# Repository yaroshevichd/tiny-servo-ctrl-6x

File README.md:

It's a try to make PWM controller on X channel using AVR MCU. MCU communication is I2C.

At local market ATtiny44A is cheapeast one, plus it have enough pins to drive 6 servos, communicate using TWI, and 3 pins to custimze address. So it's possible to drive up to (2^3 - 1) * 6 = 42 servo, which is more than enough for my requirements.

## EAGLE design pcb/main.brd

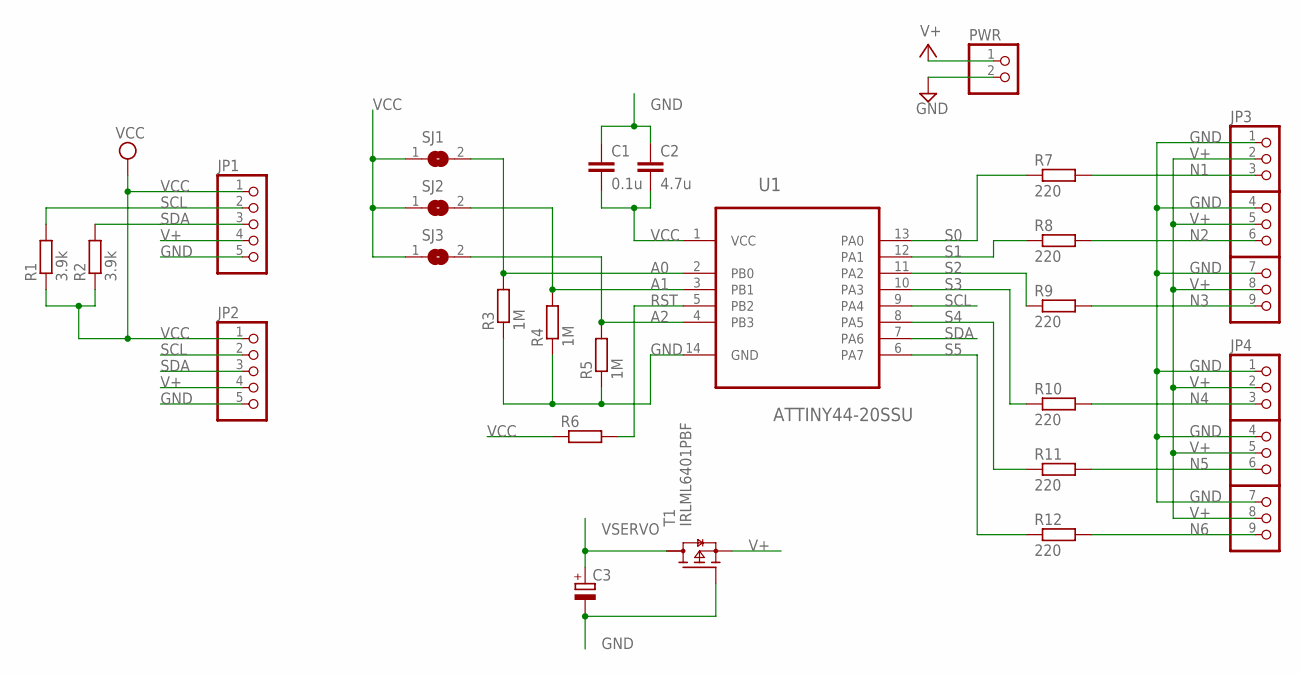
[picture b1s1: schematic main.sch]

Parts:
C1: 0.1u; C0805
C2: 4.7u; C0805
C3: CPOL-EUE2.5-6; E2,5-6
JP1, JP2: PINHD-1X5; 1X05
JP3, JP4: PINHD-3X3; 3X03
PWR: PINHD-1X2; 1X02
R1, R2: 3.9k; R0805
R3, R4, R5: 1M; R0805
R6: R-EU_R0805; R0805
R7, R8, R9, R10, R11, R12: 220; R0805
SJ1, SJ2, SJ3: SJ
T1: IRLML6401PBF; SOT23
U1: ATTINY44-20SSU; SOIC127P600X175-14N

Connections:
A0: R3.2, SJ1.2, U1.2 (PB0)
A1: R4.2, SJ2.2, U1.3 (PB1)
A2: R5.2, SJ3.2, U1.4 (PB3)
GND: C1.1, C2.1, C3.-, JP1.5, JP2.5, JP3.1, JP3.4, JP3.7, JP4.1, JP4.4, JP4.7, PWR.2, R3.1, R4.1, R5.1, T1.1 (G), U1.14 (GND)
N1: JP3.3, R7.2
N2: JP3.6, R8.2
N3: JP3.9, R9.2
N4: JP4.3, R10.2
N5: JP4.6, R11.2
N6: JP4.9, R12.2
RST: R6.2, U1.5 (PB2)
S0: R7.1, U1.13 (PA0)
S1: R8.1, U1.12 (PA1)
S2: R9.1, U1.11 (PA2)
S3: R10.1, U1.10 (PA3)
S4: R11.1, U1.8 (PA5)
S5: R12.1, U1.6 (PA7)
SCL: JP1.2, JP2.2, R1.2, U1.9 (PA4)
SDA: JP1.3, JP2.3, R2.2, U1.7 (PA6)
V+: JP1.4, JP2.4, JP3.2, JP3.5, JP3.8, JP4.2, JP4.5, JP4.8, PWR.1, T1.2 (S)
VCC: C1.2, C2.2, JP1.1, JP2.1, R1.1, R2.1, R6.1, SJ1.1, SJ2.1, SJ3.1, U1.1 (VCC)
VSERVO: C3.+, T1.3 (D)

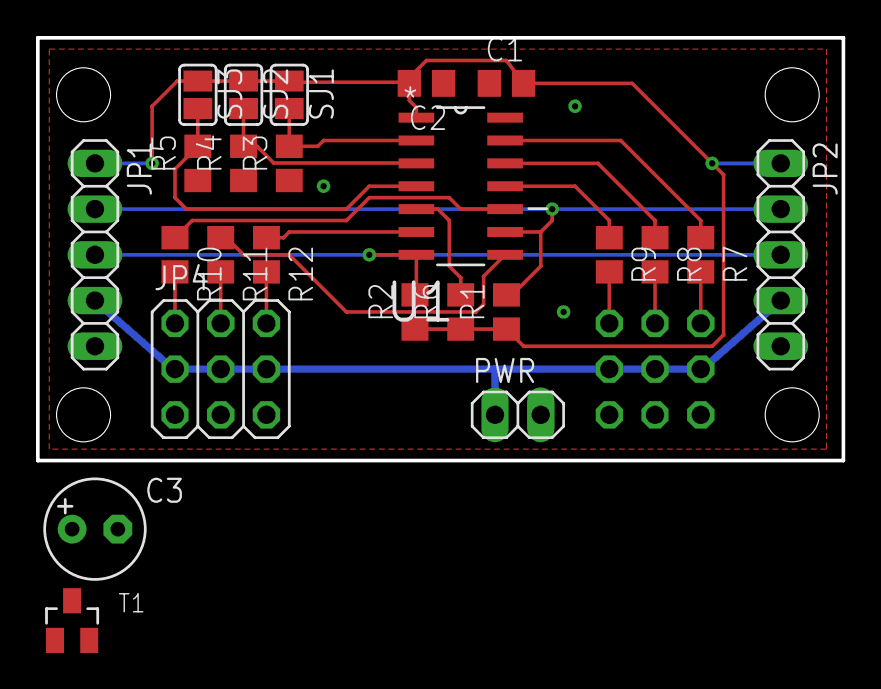
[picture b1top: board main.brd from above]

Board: 2 copper layers, 44.8 x 23.5 mm, 25 parts (1 on the bottom side), 22 nets.

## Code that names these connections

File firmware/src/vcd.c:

#include <avr/io.h>
#include "avr_mcu_section.h"

AVR_MCU(F_CPU, "attiny44");
AVR_MCU_VCD_FILE("tiny_servo_6x.vcd", 1);

const struct avr_mmcu_vcd_trace_t _AVR_MMCU_SERVO[]  _MMCU_ = {
    { AVR_MCU_VCD_SYMBOL("SERVO-0"), .mask = _BV(PA0), .what = (void*)&PORTA, },
    { AVR_MCU_VCD_SYMBOL("SERVO-1"), .mask = _BV(PA1), .what = (void*)&PORTA, },
    { AVR_MCU_VCD_SYMBOL("SERVO-2"), .mask = _BV(PA2), .what = (void*)&PORTA, },
    { AVR_MCU_VCD_SYMBOL("SERVO-3"), .mask = _BV(PA3), .what = (void*)&PORTA, },
    { AVR_MCU_VCD_SYMBOL("SERVO-4"), .mask = _BV(PA5), .what = (void*)&PORTA, },
    { AVR_MCU_VCD_SYMBOL("SERVO-5"), .mask = _BV(PA7), .what = (void*)&PORTA, },
    { AVR_MCU_VCD_SYMBOL("OCR1A"), .what = (void*)&OCR1A, },
    { AVR_MCU_VCD_SYMBOL("TCCR0B"), .what = (void*)&TCCR0B, },
    { AVR_MCU_VCD_SYMBOL("TCNT1L"), .what = (void*)&TCNT1L, },
    { AVR_MCU_VCD_SYMBOL("TCCR1B"), .what = (void*)&TCCR1B, },
};

AVR_MCU_VCD_IRQ_TRACE(6, 1, "TIM1_COMPA");
AVR_MCU_VCD_IRQ_TRACE(9, 1, "TIM0_COMPA");

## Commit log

2019-05-14 PCB Design added
2019-05-14 Firmware for ATtiny44A added
2019-05-16 * Fix "unsigned int" overflow while calculate pulse length * Drop TWI transmit buffer before send new response
2019-05-16 Update firmware README to reflect current implementation
2019-05-16 Fix firmware README nested lists formatting
